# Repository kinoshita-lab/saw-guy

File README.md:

# Saw Guy

A tiny analog sawtooth VCO on a 40 × 40 mm board, powered by a CR2032 coin cell.
Press the button and it plays: a raw sawtooth from the on-board speaker and the
3.5 mm jack, with an LED that follows the waveform.

| Top | Bottom |
| --- | --- |
|  |  |

Demo video: [images/movie.mp4](images/movie.mp4)

## Features

- Analog sawtooth oscillator with an exponential (transistor-pair) pitch converter
- Single pitch knob, sweeping from slow sub-audio ticks (the LED visibly blinks) up into the audio range
- External CV input (2-pin header) summed into the pitch control
- On-board speaker and 3.5 mm audio output, both active at the same time
- Red LED whose brightness follows the sawtooth
- Momentary **play** button plus a **HOLD** switch for continuous sound
- Runs on a single CR2032 (3 V); the battery is only connected while the button is pressed or HOLD is on, so there is no standby drain

## Controls

| # | Part | Function |
| --- | --- | --- |
| 1 | HOLD switch (SW1) | Plays continuously |
| 2 | Push button (SW2) | Plays while pressed |
| 3 | Knob (RV1) | Pitch |
| 4 | 3.5 mm jack (J2) | Audio output (mono, on the tip) |
| 5 | Speaker (LS1) | Built-in speaker |

On the top edge there is a 2-pin **CV** header (J3, marked `+`). A positive
voltage on `+` raises the pitch. The input goes through 100 kΩ into the knob's
wiper, so it adds to the knob position. The response is exponential, but it is
not calibrated to 1 V/oct and also has no temperature compensation.

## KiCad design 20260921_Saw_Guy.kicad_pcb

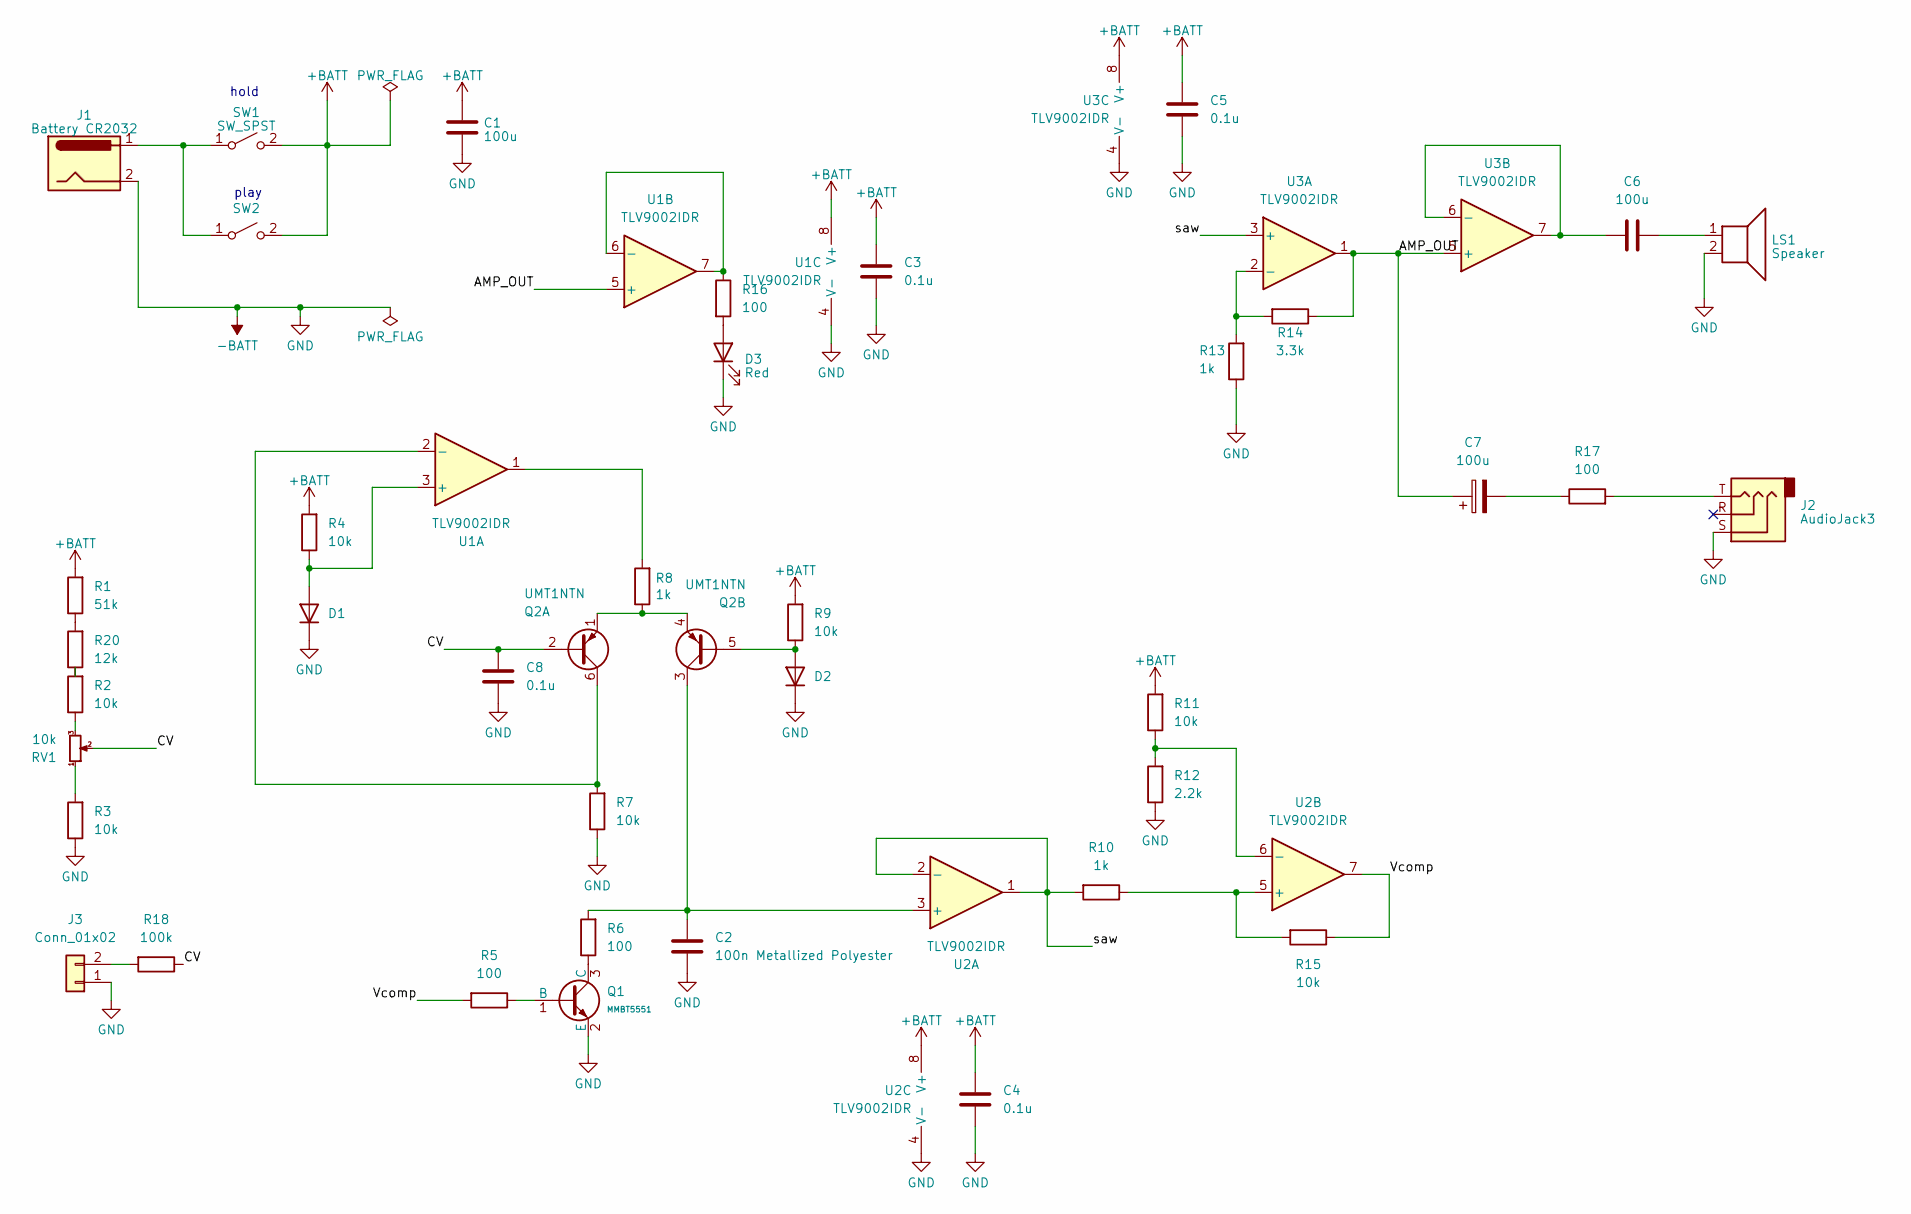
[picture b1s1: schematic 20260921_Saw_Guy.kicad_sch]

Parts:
C1, C6: 100u; C_1206_3216Metric; LCSC C15008
C2: 100n Metallized Polyester; C_PE104J2A0505_C20611475; LCSC C20611475
C3, C4, C5, C8: 0.1u; C_0402_1005Metric_Pad0.74x0.62mm_HandSolder; LCSC C1525
C7: 100u; CP_Elec_5x5.4; LCSC C18221491
D1, D2: D_SOD-523; LCSC C2965561
D3: Red; LED_0603_0402_HandSoldering_easier; LCSC C2286
J1: Battery CR2032; BatteryHolder_BS-02-A1AJ006_C964745; LCSC C964745
J2: AudioJack3; AudioJack_3.5mm_TRS_SMD_C18594; LCSC C18594
J3: Conn_01x02; PinHeader_1x02_P2.54mm_Vertical
LS1: Speaker; Speaker_Huaneng QMB-09B-03_C96256; LCSC C96256
Q1: MMBT5551; Q_SOT-23; Part MMBT5551; LCSC C408396
Q2: UMT1NTN; SOT-363_SC-70-6; LCSC C51585
R1: 51k; R_0402_1005Metric; LCSC C25794
R2, R3, R4, R7, R9, R11, R15: 10k; R_0402_1005Metric; LCSC C25744
R5, R6, R16, R17: 100; R_0402_1005Metric; LCSC C25076
R8, R10, R13: 1k; R_0402_1005Metric; LCSC C11702
R12: 2.2k; R_0402_1005Metric; LCSC C25879
R14: 3.3k; R_0402_1005Metric; LCSC C25890
R18: 100k; R_0402_1005Metric; LCSC C25741
R20: 12k; R_0402_1005Metric; LCSC C25752
RV1: 10k; POT_3386K; LCSC C330583
SW1: SW_SPST; SW_SLIDE_DPDT_XUNPU SS-2235-H2.0_C7501621; LCSC C7501621
SW2: SW_SPST; SW_Tactile_6mm_x_6mm_Futsuuno_SMD; LCSC C294565
U1, U2, U3: TLV9002IDR; SOIC-8_3.9x4.9mm_P1.27mm; LCSC C398360

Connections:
+BATT: C1.1, C3.1, C4.1, C5.1, R1.2, R4.2, R9.2, R11.2, SW1.2 (B), SW2.2 (B), U1.8 (V+), U2.8 (V+), U3.8 (V+)
-BATT: C1.2, C2.2, C3.2, C4.2, C5.2, C8.2, D1.1 (K), D2.1 (K), D3.1 (K), J1.2, J2.S, J3.1, LS1.2, Q1.2 (E), R3.1, R7.1, R12.1, R13.1, U1.4 (V-), U2.4 (V-), U3.4 (V-)
/AMP_OUT: C7.1, R14.1, U1.5 (+), U3.1, U3.5 (+)
/CV: C8.1, Q2.2 (B1), R18.1, RV1.2
/Vcomp: R5.2, R15.1, U2.7
/saw: R10.2, U2.1, U2.2 (-), U3.3 (+)
unnamed: C6.2, LS1.1
unnamed: C7.2, R17.1
unnamed: D1.2 (A), R4.1, U1.3 (+)
unnamed: D2.2 (A), Q2.5 (B2), R9.1
unnamed: D3.2 (A), R16.2
unnamed: J2.T, R17.2
unnamed: J3.2, R18.2
unnamed: Q1.1 (B), R5.1
unnamed: Q1.3 (C), R6.1
unnamed: Q2.6 (C1), R7.2, U1.2 (-)
unnamed: Q2.1 (E1), Q2.4 (E2), R8.1
unnamed: C2.1, Q2.3 (C2), R6.2, U2.3 (+)
unnamed: R1.1, R20.2
unnamed: R2.1, RV1.3
unnamed: R2.2, R20.1
unnamed: R3.2, RV1.1
unnamed: R8.2, U1.1
unnamed: J1.1, SW1.1 (A), SW2.1 (A)
unnamed: R16.1, U1.6 (-), U1.7
unnamed: R10.1, R15.2, U2.5 (+)
unnamed: R11.1, R12.2, U2.6 (-)
unnamed: R13.2, R14.2, U3.2 (-)
unnamed: C6.1, U3.6 (-), U3.7

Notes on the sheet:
hold
play

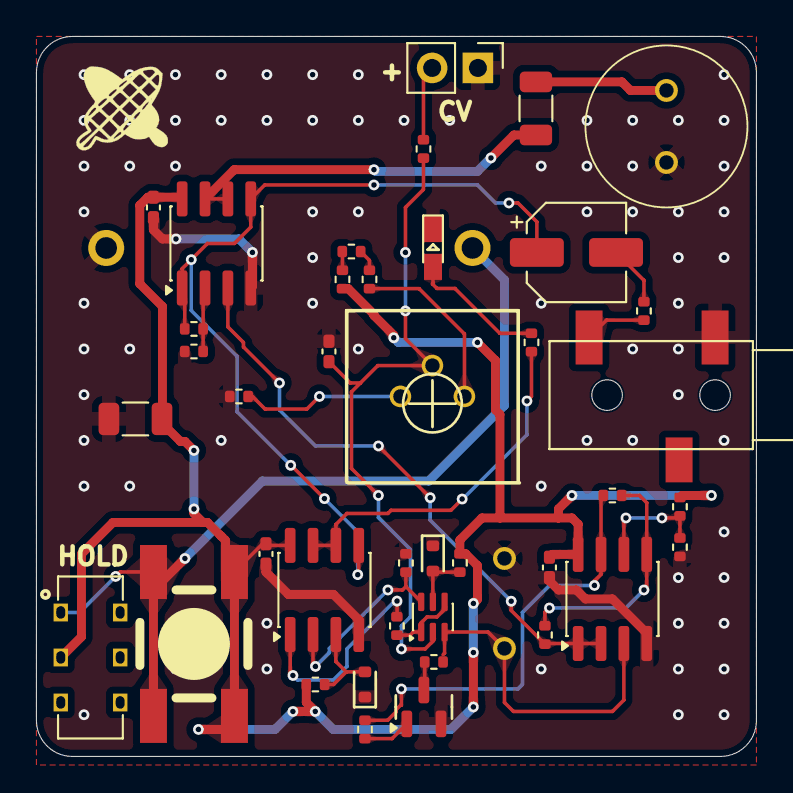
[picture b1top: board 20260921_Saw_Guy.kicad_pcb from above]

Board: 2 copper layers, 40.0 x 40.0 mm, 42 parts (1 on the bottom side), 29 nets.
